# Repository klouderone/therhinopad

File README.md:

# The Rhino Macropad by Kea Workshop

The Rhino Pad is a compact Macro Pad tailored for Computer-Aided Drawing, with 13 keys and an encoder that can be programmed for any macro in your program. It supports QMK or ZMK with either a Pro Micro or similar for QMK, or the Nice!Nano V2 for ZMK. The Keycap spacing is 19.05mm x 19.05mm, NOT the usual choc keycap spacing. You can find the 3D printed keycaps on printables https://www.printables.com/model/685983-kea-workshop-choc-v1-mx-spaced-keycaps. 

**Features:**

- 13 Switches, 1 Encoder
- Pro Micro footprint
- Supports MX and Choc Hotswap Switches
- Supports wireless Microcontrollers (nice!nano); built in battery pads and battery switch pads
- Magnetic Sandwich Case (20x 3mm Diameter x 2mm Height)

## Build Guide

This build is a medium-hard build. It is recommended that you use solder paste for the diodes, as it takes patience and a steady hand to solder them using an Iron.

**PLEASE MAKE SURE TO READ THE WHOLE GUIDE BEFORE COMMENCING BUILD.**

**Parts Needed:**
- 1x Rhino Macropad PCB
- 13x Kailh Choc Hot Swap Sockets
- 2x B3U-1000P Tactile Button (extra for mistake)
- 26x Mill-Max Pins
- 2x 13 Pin Mill-Max Sockets
- 20x 1N4148 SOD-123 Diodes (extra for mistakes)
- 1x EC11 Encoder
- 1x 3 Pin Toggle Switch (MSK-12C02 & PCM12SMTR)
- 13x Choc switches
- 13x Choc keycaps
- 1x Microcontroller (Elite C/Pro Micro/Nice!Nano V2)
- 1x OLED Display with matching header (optional)

### STEP ZERO: Flash Microcontroller with Known Firmware

First thing to do is to flash the microcontroller with the given firmware. This is to ensure that the Microcontroller works properly, and if it doesn't, is returnable/refundable to the vendor you bought it from. If you are using QMK, download the QMK toolbox and the VIAL firmware for your microcontroller, .uf2 for Elite-C RP2040 controllers, or .hex for Pro-Micro ATMega32U4 controllers. A google will be able to show you how to flash for your microcontroller. 

### STEP ONE: Soldering the Reset Button

Soldering the reset button is the most difficult due to its small contacts, though it is not required for the board to work. If you do not want to solder the reset button, you just need to bridge the pads on the back of the board with tweezers to put it into bootloader mode. Carefully and steadily use tweezers to correctly align the button, heat up the tinned pad and place the button onto the pad, remove the heat and let the solder solidify. Then solder the other pad to secure, and possibly add a touch more solder on the first pad.

### STEP TWO: Soldering the Battery Switch (wireless version only)

Soldering the battery switch is a little more complex than the reset button. I reccommend solder paste for this. If you do not use solder paste, tin one pad first. Place the switch onto the pad and hold it steady using tweezers, heat it up, and push it into the solder and let it solidify. Carefully solder all other pads to the PCB.

### STEP THREE: Soldering the diodes 

There are two ways to do this, both require tweezers;

Option One: using solder paste and a heat gun (hairdryer may work)

Apply solder paste into all the diode pads. Use your tweezers to carefully place the diodes in the correct orientation on top of the pads. Gently apply heat using a hot plate or a heat gun, and watch the diodes pull themselves into place.

Option Two: using, a clean soldering iron, a steady hand, and patience.

Tin the top pad of all the diode pads. Carefully and steadily use tweezers hold and correctly align the diode, heat up the tinned pad, and place the diode onto the pad. Then, solder the other pad to secure. 

### STEP FOUR: Solder Hotswap Sockets

Tin one of the Hotswap pads. Place your hotswap socket into the holes, and heat up the tinned pad side while adding solder. Make sure to touch the pad or the contact of the hotswap socket that is on the pad. After a good connection, remove heat and solder other side. Repeat for all. I recommend pushing the hotswap socket in while soldering to get a good solder joint.

### STEP FIVE: Soldering Mill-Max sockets to PCB

To do this correctly, you want to put the sockets into the PCB holes (see photo below for placement depending on microcontroller), and put the Microcontroller on top to align them perpendicular to the PCB. Use putty or your finger to keep the sockets aligned and solder them into place.

If you are using a nice!nano or similar, you need a 13 pin socket, as the top pins are used as the battery pins, so that you can switch off and on the battery. If you are not using a nice!nano or similar, you only need a 12 pin socket, so simply snip off the extra socket and solder.  

### STEP SIX: Soldering Microcontroller to the Mill-Max Pins

Place the microcontroller onto the sockets, aligning the pins with the through-holes as shown, and carefully solder. Make sure you do not leave the iron on the pins/through-holes for too long, as you risk burning the traces of the microcontoller. Be sure to not use too much solder, as if you use too much it can flow down through the hole and join the socket and microcontroller. It is better to do too little and go back after later. Carefully remove the microcontroller to confirm that the joints are good. When removing, pull uniformly from both the USB side and the bottom side. Failure to do this can result in bending the Mill-Max pins. I have found using a switch puller to be handy doing this.

### STEP SEVEN: Soldering Display Pins

On the PCB, the display pins are noted of their output. If you are using an OLED display, disregard the CS pin (this is used for e-paper displays like the nice!view). If you are using Mill-Max sockets, you want a PH5 (plastic height 5) box header.  You can then solder the box header. 

### STEP EIGHT: Soldering the Encoder

Make sure the Encoder is flat up against the PCB when soldering. First solder the signal pins (as they require less heat than the locking pins) to hold the encoder in place, and then solder the locking pins. 

### STEP NINE: Soldering the Battery (wireless version only)

With the microcontroller out of the Mill-Max sockets, carefully solder the positive lead of the battery to the positive pad, and the negative lead to the negative pad. DO NOT LET THESE TWO LEADS TOUCH! 

### STEP TEN: 

Reinsert your microcontroller, install your switches and keycaps, and enjoy your new Macropad!

## Photos

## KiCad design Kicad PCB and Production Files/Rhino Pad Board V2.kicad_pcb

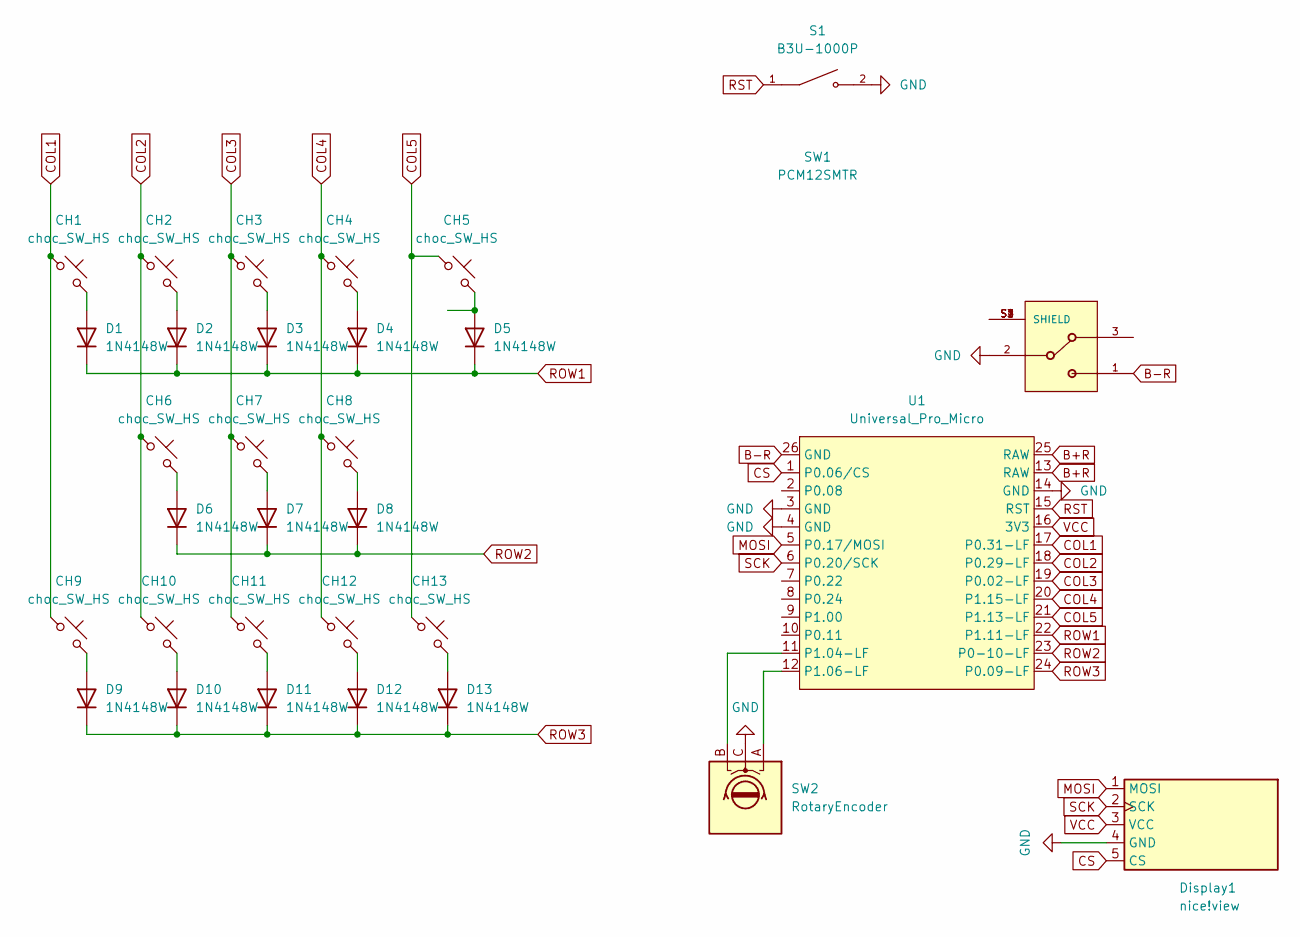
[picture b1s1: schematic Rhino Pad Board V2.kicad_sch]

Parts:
CH1, CH2, CH3, CH4, CH5, CH6, CH7, CH8, CH9, CH10, CH11, CH12, CH13: choc_SW_HS; SW_choc_v1_HS_1u
D1, D2, D3, D4, D5, D6, D7, D8, D9, D10, D11, D12, D13: 1N4148W; D_SOD-123
Display1: nice!view; nice_view
S1: B3U-1000P; SW_SPST_B3U-1000P
SW1: PCM12SMTR; MSK-12C02 Toggle Switch
SW2: RotaryEncoder; RotaryEncoder_Alps_EC12E_Vertical_H20mm
U1: Universal_Pro_Micro; Universal_Pro_Micro_Footprint

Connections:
B+R: U1.13 (RAW), U1.25 (RAW)
B-R: SW1.1, U1.26 (GND)
COL1: CH1.1, CH9.1, U1.17 (P0.31-LF)
COL2: CH2.1, CH6.1, CH10.1, U1.18 (P0.29-LF)
COL3: CH3.1, CH7.1, CH11.1, U1.19 (P0.02-LF)
COL4: CH4.1, CH8.1, CH12.1, U1.20 (P1.15-LF)
COL5: CH5.1, CH13.1, U1.21 (P1.13-LF)
CS: Display1.5 (CS), U1.1 (P0.06/CS)
GND: Display1.4 (GND), S1.2, SW1.2, SW2.C, U1.3 (GND), U1.4 (GND), U1.14 (GND)
MOSI: Display1.1 (MOSI), U1.5 (P0.17/MOSI)
unnamed: CH1.2, D1.2 (A)
unnamed: CH2.2, D2.2 (A)
unnamed: CH3.2, D3.2 (A)
unnamed: CH4.2, D4.2 (A)
unnamed: CH5.2, D5.2 (A)
unnamed: CH6.2, D6.2 (A)
unnamed: CH7.2, D7.2 (A)
unnamed: CH8.2, D8.2 (A)
unnamed: CH9.2, D9.2 (A)
unnamed: CH10.2, D10.2 (A)
unnamed: CH11.2, D11.2 (A)
unnamed: CH12.2, D12.2 (A)
unnamed: CH13.2, D13.2 (A)
unnamed: SW2.B, U1.11 (P1.04-LF)
unnamed: SW2.A, U1.12 (P1.06-LF)
ROW1: D1.1 (K), D2.1 (K), D3.1 (K), D4.1 (K), D5.1 (K), U1.22 (P1.11-LF)
ROW2: D6.1 (K), D7.1 (K), D8.1 (K), U1.23 (P0-10-LF)
ROW3: D9.1 (K), D10.1 (K), D11.1 (K), D12.1 (K), D13.1 (K), U1.24 (P0.09-LF)
RST: S1.1, U1.15 (RST)
SCK: Display1.2 (SCK), U1.6 (P0.20/SCK)
VCC: Display1.3 (VCC), U1.16 (3V3)

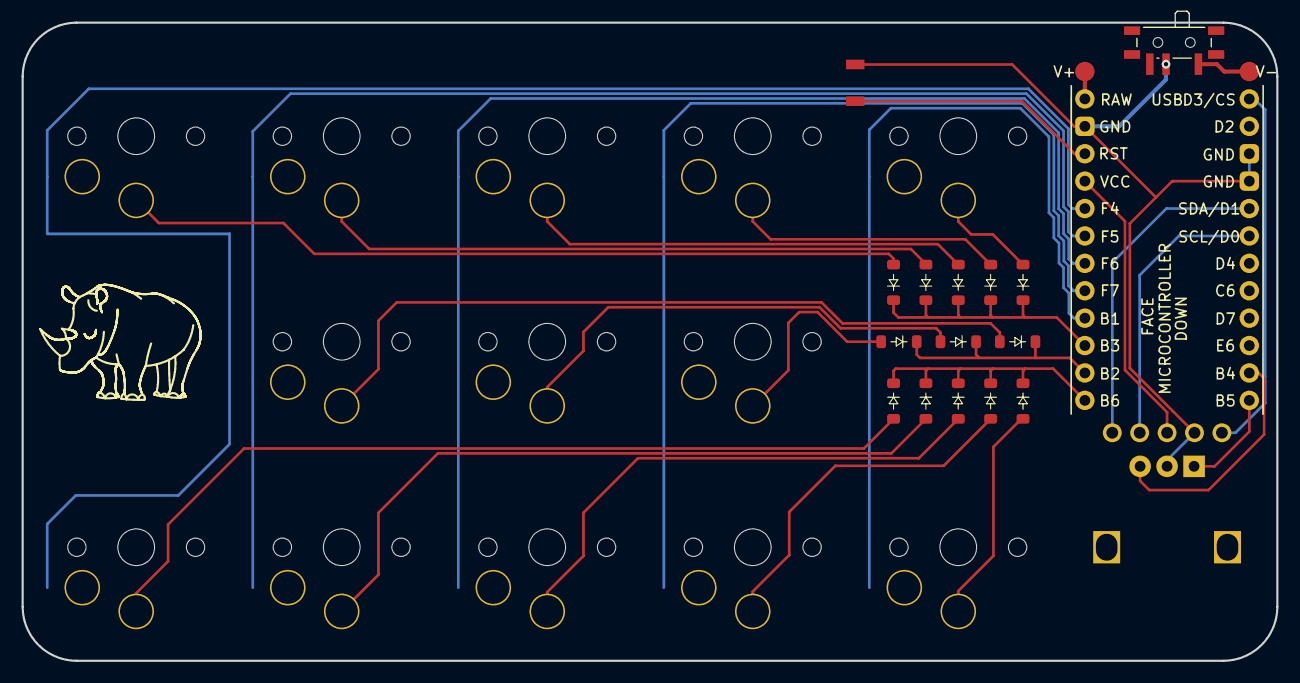
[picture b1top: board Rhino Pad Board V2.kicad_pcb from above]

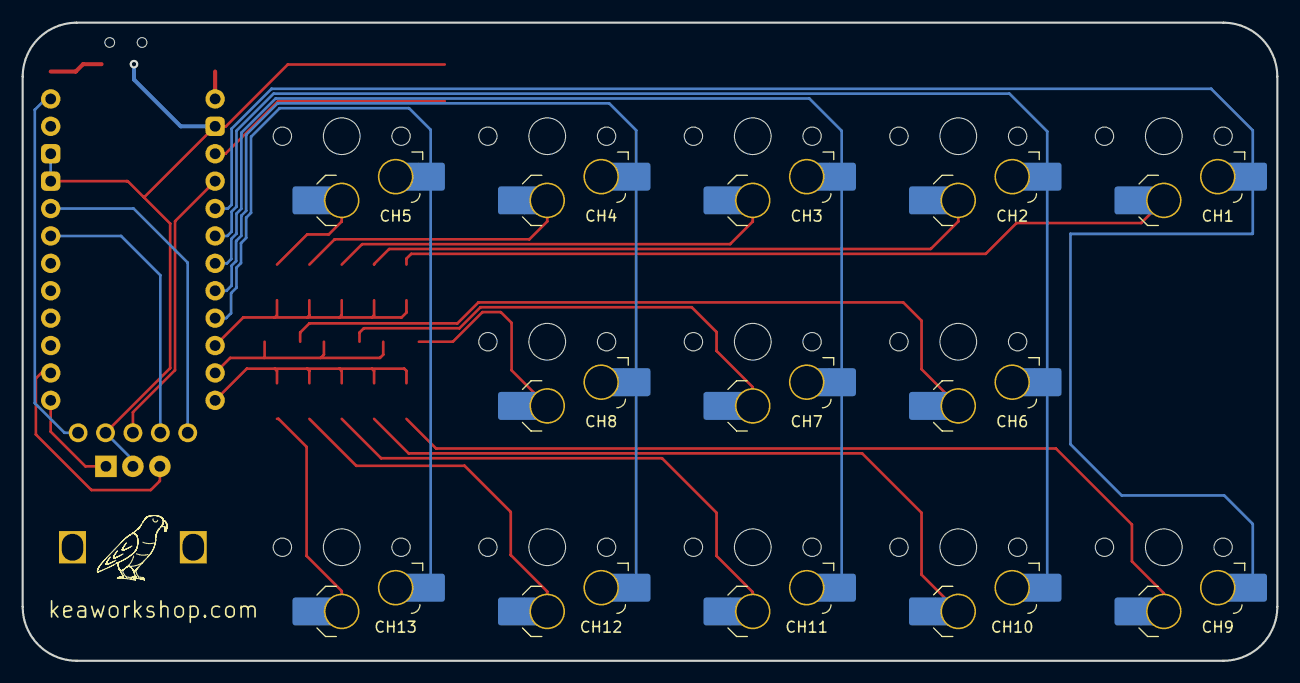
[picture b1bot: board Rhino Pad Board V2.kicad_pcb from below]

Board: 2 copper layers, 116.3 x 59.2 mm, 31 parts (13 on the bottom side), 31 nets.

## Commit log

2024-02-08 Case
2024-11-14 update to microcontroller footprint
